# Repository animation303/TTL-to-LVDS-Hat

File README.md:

# TTL-to-LVDS-Hat
Hat for Raspberry Pi that converts RGB TTL to LVDS for the Tianma 12.3" 1920x720 Bar LCD found in various Chinese vehicle instrument clusters.

based on https://github.com/exentio/koyomi-lvds-hat

Board untested until I can get some made.

TODO: config.txt settings, will have to wait until boards are in hand
TODO: Backlight Circuit
TODO: clean up schematic, its a mess

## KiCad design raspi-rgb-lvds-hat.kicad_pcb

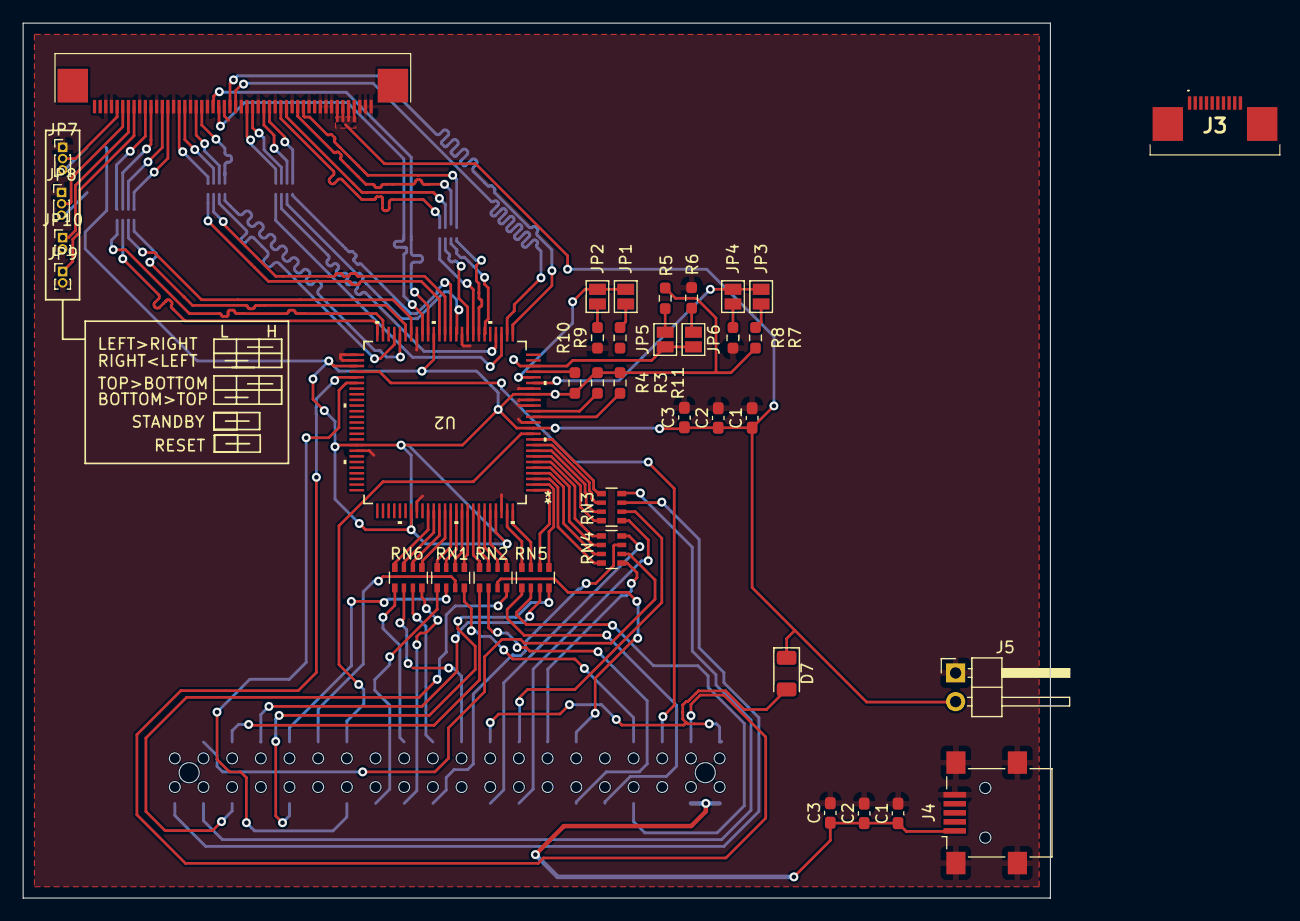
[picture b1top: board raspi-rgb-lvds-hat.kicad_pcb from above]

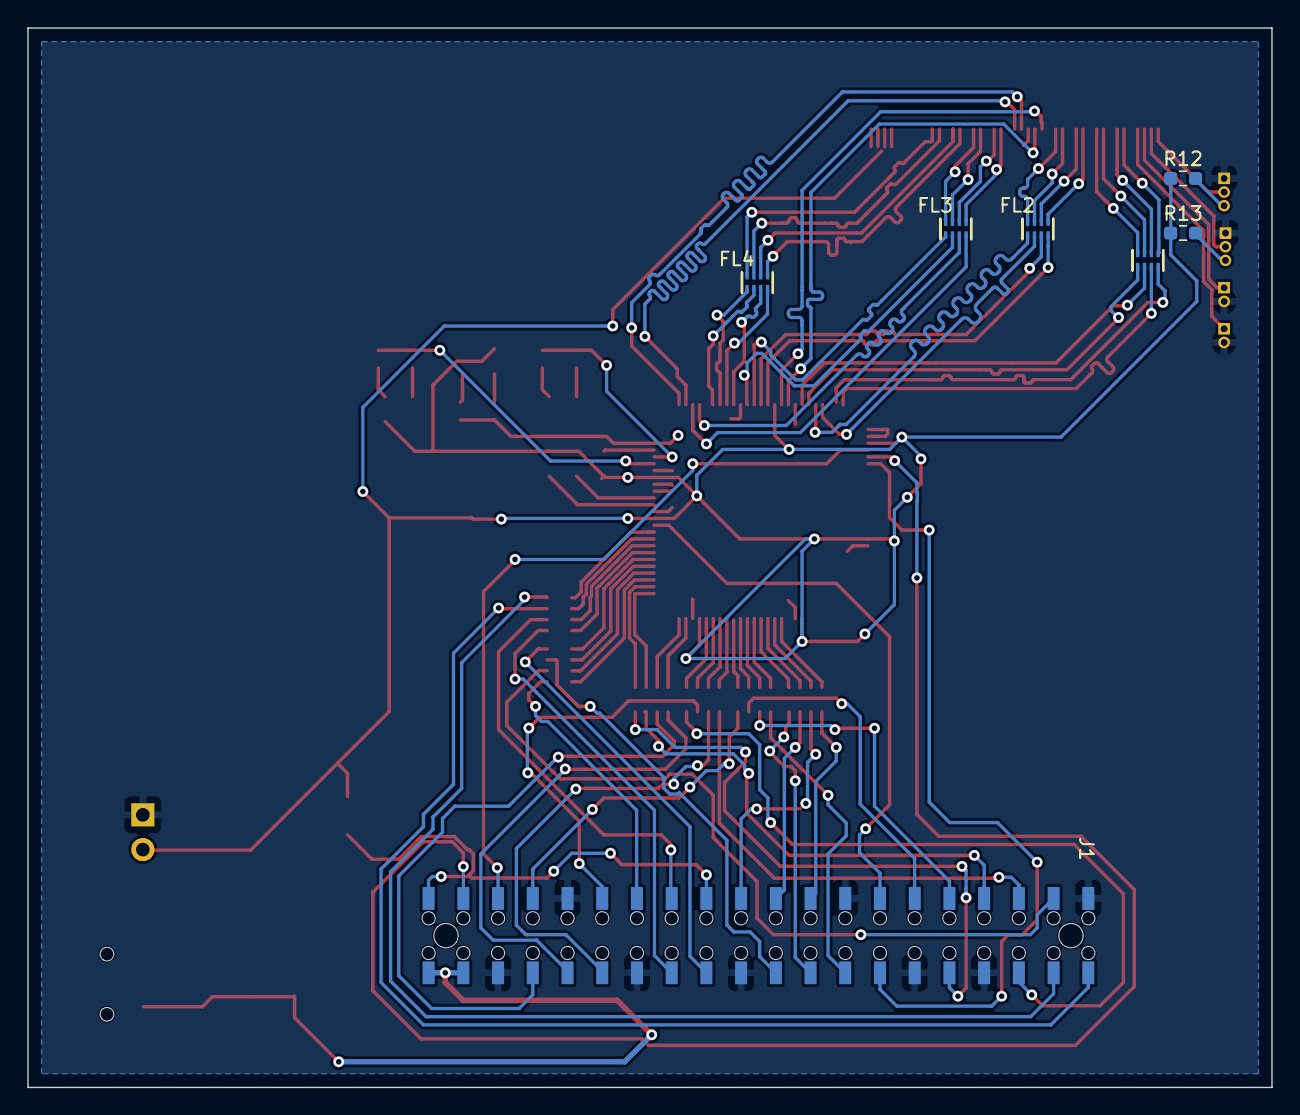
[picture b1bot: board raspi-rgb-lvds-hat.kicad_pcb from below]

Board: 2 copper layers, 91.0 x 77.5 mm, 44 parts (7 on the bottom side), 107 nets.

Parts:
C1, C1#2: 1uF; C_0603_1608Metric_Pad1.08x0.95mm_HandSolder
C2, C2#2: 100nF; C_0603_1608Metric_Pad1.08x0.95mm_HandSolder
C3, C3#2: 10nF; C_0603_1608Metric_Pad1.08x0.95mm_HandSolder
D7: D_1206_3216Metric
FL1, FL2, FL3, FL4: DLP2ADN121HL4L; Murata_DLP2ADN121HL4L
J1: RPi_GPIO; Samtec_HLE-120-02-XXX-DV-BE-XX-XX
J2: 68715014022
J3: 68711014022
J4: USB_B_Micro; USB_Mini-B_Lumberg_2486_01_Horizontal
J5: Conn_01x02_Pin; PinHeader_1x02_P2.54mm_Horizontal
JP1, JP2, JP3, JP4, JP5, JP6: SolderJumper_2_Open; SolderJumper-2_P1.3mm_Open_Pad1.0x1.5mm
JP7, JP8: Jumper_3_Open; PinHeader_1x03_P1.00mm_Vertical
JP9, JP10: Jumper_2_Open; PinHeader_1x02_P1.00mm_Vertical
R3, R4, R5, R6, R7, R8, R9, R10: 10K / 1%; R_0603_1608Metric_Pad0.98x0.95mm_HandSolder
R11: 1M; R_0603_1608Metric_Pad0.98x0.95mm_HandSolder
R12, R13: R100; R_0603_1608Metric_Pad0.98x0.95mm_HandSolder
RN1, RN2, RN3, RN4, RN5, RN6: 47; R_Array_Convex_4x0603
U2: DS90C387VJD; VJD100A_TEX

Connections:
+3V3: C1#2.1, C2.1, C3.1, D7.1, D7.2, J1.1 (3.3V), J1.17 (3.3V), J2.4 (VCC), J2.5 (VCC), J2.6 (VCC), J2.7 (VCC), J5.2, JP7.3 (B), JP8.3 (B), R3.1, R4.1, R5.1, R7.1, R9.1, R11.1, R12.1, R12.2, R13.1, R13.2, U2.12 (PLLVCC), U2.18 (PLLVCC), U2.30 (LVDSVCC), U2.40 (LVDSVCC), U2.48 (LVDSVCC), U2.53 (VCC), U2.67 (VCC), U2.82 (VCC), U2.97 (VCC)
+5V: C1.1, C2#2.1, C3#2.1, J1.2 (5V), J1.4 (5V), J4.1 (VBUS)
/NC: J2.11 (NC), J2.49 (NC), J2.50 (NC)
A0N: FL1.4, U2.50 (A0M)
A0P: FL1.2, U2.49 (A0P)
A1N: FL2.8, U2.47 (A1M)
A1P: FL2.6, U2.46 (A1P)
A2N: FL1.8, U2.45 (A2M)
A2P: FL1.6, U2.44 (A2P)
A3N: FL2.4, U2.39 (A3M)
A3P: FL2.2, U2.38 (A3P)
A4N: FL3.4, U2.37 (A4M)
A4P: FL3.2, U2.36 (A4P)
A5N: FL4.8, U2.34 (A5M)
A5P: FL4.6, U2.33 (A5P)
A6N: FL4.4, U2.32 (A6M)
A6P: FL4.2, U2.31 (A6P)
A7N: FL3.8, U2.29 (A7M)
A7P: FL3.6, U2.28 (A7P)
B0: J1.7 (BCM4_GPCLK0), RN1.8 (R1.2)
B1: J1.29 (BCM5), RN1.7 (R2.2)
B2: J1.31 (BCM6), RN1.6 (R3.2)
B3: J1.26 (BCM7_CE1), RN1.5 (R4.2)
B4: J1.24 (BCM8_CE0), RN6.8 (R1.2)
B5: J1.21 (BCM9_MISO), RN6.7 (R2.2)
B6: J1.19 (BCM10_MOSI), RN6.6 (R3.2)
B7: J1.23 (BCM11_SCLK), RN6.5 (R4.2)
B10: RN1.1 (R1.1), U2.92 (B10)
B11: RN1.2 (R2.1), U2.91 (B11)
B12: RN1.3 (R3.1), U2.90 (B12)
B13: RN1.4 (R4.1), U2.89 (B13)
B14: RN6.1 (R1.1), U2.88 (B14)
B15: RN6.2 (R2.1), U2.87 (B15)
B16: RN6.3 (R3.1), U2.86 (B16)
B17: RN6.4 (R4.1), U2.85 (B17)
CLK1N: J2.28 (ELVCKN), U2.42 (CLK1M)
CLK1P: J2.29 (ELVCKP), U2.41 (CLK1P)
CLK2N: J2.25 (OLVCKN), U2.27 (CLK2M/NC)
CLK2P: J2.26 (OLVCKP), U2.26 (CLK2P/NC)
CLKIN: J1.27 (BCM0_ID_SD), U2.11 (CLKIN)
DUAL: JP5.2 (B), JP6.2 (B), U2.23 (DUAL)
ELV0N: FL1.5, J2.40 (ELV0N)
ELV0P: FL1.7, J2.41 (ELV0P)
ELV1N: FL2.1, J2.31 (ELV1N)
ELV1P: FL2.3, J2.32 (ELV1P)
ELV2N: FL1.1, J2.37 (ELV2N)
ELV2P: FL1.3, J2.38 (ELV2P)
ELV3N: FL2.5, J2.34 (ELV3N)
ELV3P: FL2.7, J2.35 (ELV3P)
ENABLE: J1.28 (BCM1_ID_SC), U2.56 (DE)
G0: J1.32 (BCM12_PWM0), RN5.8 (R1.2)
G1: J1.33 (BCM13_PWM1), RN5.7 (R2.2)
G2: J1.8 (BCM14_TXD), RN5.6 (R3.2)
G3: J1.10 (BCM15_RXD), RN5.5 (R4.2)
G4: J1.36 (BCM16), RN2.8 (R1.2)
G5: J1.11 (BCM17), RN2.7 (R2.2)
G6: J1.12 (BCM18_PCM_C), RN2.6 (R3.2)
G7: J1.35 (BCM19_MISO_PCM_FS), RN2.5 (R4.2)
G10: RN5.1 (R1.1), U2.2 (G10)
G11: RN5.2 (R2.1), U2.1 (G11)
G12: RN5.3 (R3.1), U2.100 (G12)
G13: RN5.4 (R4.1), U2.99 (G13)
G14: RN2.1 (R1.1), U2.96 (G14)
G15: RN2.2 (R2.1), U2.95 (G15)
G16: RN2.3 (R3.1), U2.94 (G16)
G17: RN2.4 (R4.1), U2.93 (G17)
GND: C1.2, C1#2.2, C2.2, C2#2.2, C3.2, C3#2.2, J1.6 (GND), J1.9 (GND), J1.14 (GND), J1.20 (GND), J1.25 (GND), J1.30 (GND), J1.34 (GND), J1.39 (GND), J2.1 (GND), J2.2 (GND), J2.3 (GND), J2.8 (GND), J2.9 (GND), J2.10 (GND), J2.12 (GND), J2.15 (GND), J2.18 (GND), J2.21 (GND), J2.24 (GND), J2.27 (GND), J2.30 (GND), J2.33 (GND), J2.36 (GND), J2.39 (GND), J2.42 (GND), J2.47 (Fail_T), J2.48 (GND), J4.5 (GND), J4.6 (Shield), J5.1, JP7.1 (A), JP8.1 (A), JP9.2 (B), JP10.2 (B), R6.1, R8.1, R10.1, U2.13 (GND), U2.16 (PLLGND), U2.17 (PLLGND), U2.19 (PLLGND), U2.24 (BAL), U2.25 (LVDSGND), U2.35 (LVDSGND), U2.43 (LVDSGND), U2.51 (LVDSGND), U2.52 (GND), U2.68 (GND), U2.83 (GND), U2.98 (GND)
HSYNC: J1.5 (BCM3_SCL), U2.54 (HSYNC)
unnamed: J2.43 (RESET), JP9.1 (A)
unnamed: J2.44 (STNDBY), JP10.1 (A)
unnamed: JP1.1 (A), R9.2
unnamed: JP2.1 (A), R10.2
unnamed: JP3.1 (A), R7.2
unnamed: JP4.1 (A), R8.2
unnamed: JP5.1 (A), R5.2
unnamed: JP6.1 (A), R6.2
OLV0N: FL3.1, J2.19 (OLV0N)
OLV0P: FL3.3, J2.20 (OLV0P)
OLV1N: FL4.5, J2.16 (OLV1N)
OLV1P: FL4.7, J2.17 (OLV1P)
OLV2N: FL4.1, J2.13 (OLV2N)
OLV2P: FL4.3, J2.14 (OLV2P)
OLV3N: FL3.5, J2.22 (OLV3N)
OLV3P: FL3.7, J2.23 (OLV3P)
PLL_SEL: R3.2, U2.15 (PLLSEL)
PRE: R11.2, U2.14 (PRE)
R0: J1.38 (BCM20_MOSI_PCM_DI), RN3.8 (R1.2)
R1: J1.40 (BCM21_SCLK_PCM_DO), RN3.7 (R2.2)
R2: J1.15 (BCM22), RN3.6 (R3.2)
R3: J1.16 (BCM23), RN3.5 (R4.2)
R4: J1.18 (BCM24), RN4.8 (R1.2)
R5: J1.22 (BCM25), RN4.7 (R2.2)
R6: J1.37 (BCM26), RN4.6 (R3.2)
R7: J1.13 (BCM27), RN4.5 (R4.2)
R10: RN3.1 (R1.1), U2.10 (R10)
R11: RN3.2 (R2.1), U2.9 (R11)
R12: RN3.3 (R3.1), U2.8 (R12)
R13: RN3.4 (R4.1), U2.7 (R13)
R14: RN4.1 (R1.1), U2.6 (R14)
R15: RN4.2 (R2.1), U2.5 (R15)
R16: RN4.3 (R3.1), U2.4 (R16)
R17: RN4.4 (R4.1), U2.3 (R17)
R_FB: JP3.2 (B), JP4.2 (B), U2.20 (R_FB)
R_FDE: JP1.2 (B), JP2.2 (B), U2.21 (R_FDE)
SHLR: J2.45 (SHLR), JP8.2 (C)
VSYNC: J1.3 (BCM2_SDA), U2.55 (VSYNC)
/PD: R4.2, U2.22 (*PD)

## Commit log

2025-03-23 Add files via upload
    initial commit
2025-03-23 Update README.md again
